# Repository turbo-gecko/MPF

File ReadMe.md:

# MPF

The MicroProfessor MPF-1 is one of the original Z80 trainers. It was a trainer that I suspect a lot of original Z80 coders first learned how to program the Z80, and it was my first introduction to programming the Z80. There is a multitude of information about the MPF-1 on the 'net so won't repeat it here.

With a more recent desire to go back and re-learn the Z80, I have managed to get hold of a couple of MPF-1's to re-live the experience. In hindsight. I can see just how limited the MPF-1 actually is. Part of it's issues for me are:
- Getting software on and off of the MPF-1 is via the keyboard or cassette tape.
- An incredibly tiny amount of RAM. Ideal for teaching the basics but not much else.
- Not a lot of options exist for expanding the capabilities of the MPF-1.

This repo is for the hardware and software I have developed for the MPF-1 (and other clones) that help overcome these drawbacks.

## How to expand the MPF-1
The following section descibes how to expand the capabilities of the MPF-1 to make use modern conveniences like serial download, SD card storage etc.

A non-negotiable goal though, is to provide expandability without modification to the original kit. The MPF-1 is after all, a piece of vintage computer equipment, and to physically modify it would take away from it's value as a piece of history. The following expansions make use of the Z80 CPU bus that is the top left 2x20 pin header connector.

The expansion bus of choice that works very well with the MPF-1 is the retro modern RCBus by Small Computer Central, and the RC2014 bus. An adapter card is required to connect the MPF-1 to the expansion bus and the designs are included in the Z80 Bus to RCBus folder.

### Basic expansion bus
A basic expansion bus will require as a minimum:
- RCBus backplane. The one in the photo is an SC112 https://smallcomputercentral.com/sc112-modular-backplane-rc2014/
- A power supply for the backplane. The one in the photo is an SC142 that has been modified to switch the incoming 9VDC to the MPF-1. This allows a single switch to power on/off the complete system. https://smallcomputercentral.com/sc142-power-module-rc2014/
- 40 pin ribbon cable to connect the MPF-1 to the backplane via the adapter.

This provides the necessary backplane, power and connectivity to expand the MPF-1.

### Adding additional memory
The MPF-1 comes with 2K of RAM fitted from 1800H to 1FFFH. This is insufficient for use with an expansion bus so the first card that should be obtained is a memory expansion card with a minimum of 32K such as:
- The 64K RAM module at https://z80kits.com/shop/64k-ram-module/ is a good choice. This is the module that is fitted in the backplane in the photo's. It has been configured to provide RAM from 4000H through to FFFFH, an additional 48K!
- Another module that I have experimented with is the Paged RAM module at https://smallcomputercentral.com/sc150-paged-ram-module-rc2014/. This can provide 32K from 8000H to FFFFH.

### High speed serial
The main way to enter programs into the MPF-1 is via the keypad as machine code. Whilst it is how the MPF-1 was envisaged to be used, it is a painfully slow and error-prone way of transferring programs to the MPF-1.

The expansion bus allows a serial card to be added and along with a hex download program, can make downloading hex files to the MPF-1 very easy and straightforward. The serial card in the photo's is an ACIA single serial card. https://smallcomputercentral.com/sc139-serial-68b50-module-rc2014/

### SD card storage
The only way to load and save programs with the MPF-1 is via audio files, traditionally on tape. Whilst there are modern ways around this, it is very slow, and you would need a program to convert compiled programs to an audio format.

To store and load files using an SD card only requires an I/O card and an Adafruit style SD card adapter. The I/O card in the photo is an SC129 https://smallcomputercentral.com/sc129-digital-i-o-rc2014/.

### Putting it all together
In the Software/Option ROM/ folder https://github.com/turbo-gecko/MPF/tree/main/Software/Option%20ROM is a binary file of an EPROM image that has the following software ready to run:
- 2000H - Hex download program.
- 2222H - Memory finder program.
- 2400H - Mini SD card reader program for loading files from slots 0-9 on the first SD carc virtual disk.

Burn the binary image to a 2732 EPROM and place it in the U7 socket on the MPF-1.

### Configuration

#### Serial
The software has been designed to work with an ACIA serial card only (more in the works) at I/O address C8H. The hex load and SD card programs are designed to use the serial card at 115kbps with RTS/CTS handshaking. There is further information on the serial card at https://github.com/turbo-gecko/MPF/tree/main/Software/Hex%20Load

#### SD Card
The I/O card should be configured to use address FDH, however this can be modified along with the pin configurations in the spi_IO.ASM file at https://github.com/turbo-gecko/MPF/tree/main/Software/Library.

Default pin configurations as follows:
| I/O | Pin | Description |
| --- | --- | ----------- |
| In  |  7  | MISO        |
| Out |  0  | MOSI        |
| Out |  1  | CLK         |
| Out |  2  | CS          |

Make sure that the SD card module is designed to run off 5VDC and has the 3V3 reg on board to drive the SD card correctly.

### Using the expansion cards
Once you have everything up and running, including the U7 ROM, you can try using the hex load program at 2000H to download the 'HELPUS' example (helpus.hex) from https://github.com/turbo-gecko/MPF/tree/main/Software/Work%20Book%20Examples. Download the hex file and run the program at 1800H.

### Troubleshooting
- Start with the backplane, power supply and ribbon cable first. Make sure that when both the backplane and the MPF-1 is powered on, the MPF-1 works as normal.
- Power off the system, add the expansion cards one at a time, power back on and confirm the MPF-1 is working. If it isn't check
  - The ribbon cable is connected correctly. Pin 1 on the MPF-1 is at the top, Pin 1 on the adapter card is towards the 45 degree angle on the PCB. (See photo for details)
  - The expansion card is seated correctly in the backplane.

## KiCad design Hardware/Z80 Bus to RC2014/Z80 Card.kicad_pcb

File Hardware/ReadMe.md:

# Hardware Stuff

## Bezel - 3D Printer files
Bezel for the 7 segment display to hold the red filter lens in place.

## Z80 Bus to RCBus
Adapter card to enable the use of an RCBus or RC2014 style backplane to extend the Z80 bus of the MPF-1.

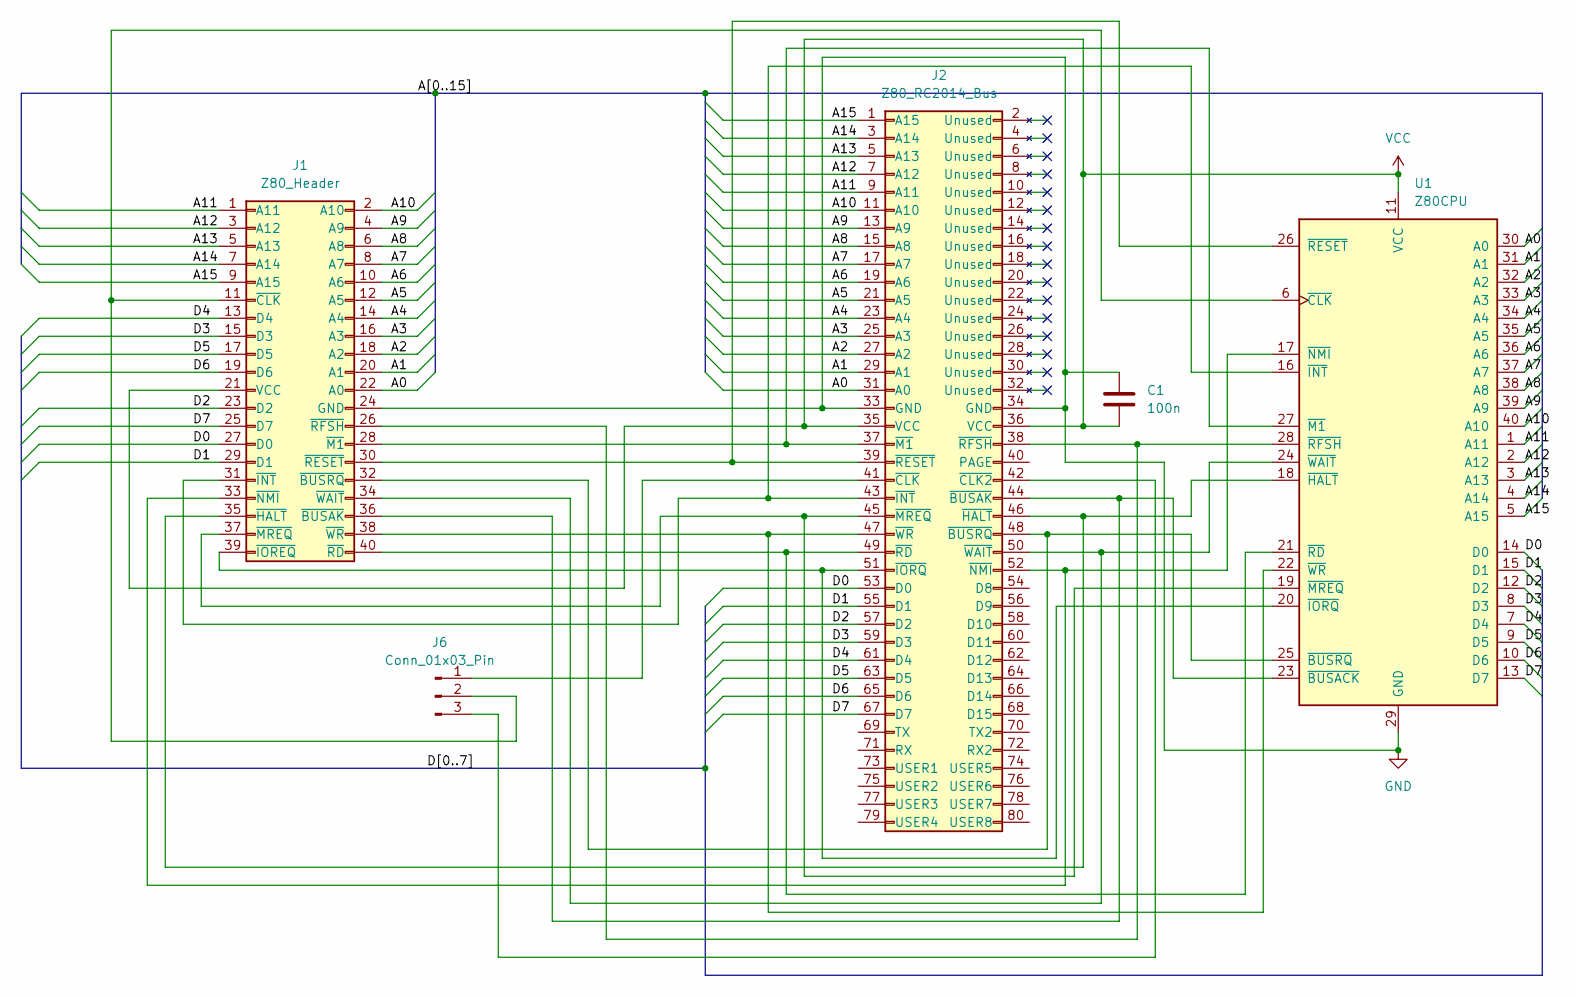
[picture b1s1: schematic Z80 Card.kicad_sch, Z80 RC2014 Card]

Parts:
C1: 100n; C_Rect_L4.0mm_W2.5mm_P2.50mm
J1: Z80_Header; PinSocket_2x20_P2.54mm_Vertical
J2: Z80_RC2014_Bus; PinSocket_2x40_P2.54mm_Vertical
J6: Conn_01x03_Pin; PinHeader_1x03_P2.54mm_Vertical
U1: Z80CPU; DIP-40_W15.24mm_Socket

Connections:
/A0: J1.22 (A0), J2.31 (A0), U1.30 (A0)
/A1: J1.20 (A1), J2.29 (A1), U1.31 (A1)
/A2: J1.18 (A2), J2.27 (A2), U1.32 (A2)
/A3: J1.16 (A3), J2.25 (A3), U1.33 (A3)
/A4: J1.14 (A4), J2.23 (A4), U1.34 (A4)
/A5: J1.12 (A5), J2.21 (A5), U1.35 (A5)
/A6: J1.10 (A6), J2.19 (A6), U1.36 (A6)
/A7: J1.8 (A7), J2.17 (A7), U1.37 (A7)
/A8: J1.6 (A8), J2.15 (A8), U1.38 (A8)
/A9: J1.4 (A9), J2.13 (A9), U1.39 (A9)
/A10: J1.2 (A10), J2.11 (A10), U1.40 (A10)
/A11: J1.1 (A11), J2.9 (A11), U1.1 (A11)
/A12: J1.3 (A12), J2.7 (A12), U1.2 (A12)
/A13: J1.5 (A13), J2.5 (A13), U1.3 (A13)
/A14: J1.7 (A14), J2.3 (A14), U1.4 (A14)
/A15: J1.9 (A15), J2.1 (A15), U1.5 (A15)
/D0: J1.27 (D0), J2.53 (D0), U1.14 (D0)
/D1: J1.29 (D1), J2.55 (D1), U1.15 (D1)
/D2: J1.23 (D2), J2.57 (D2), U1.12 (D2)
/D3: J1.15 (D3), J2.59 (D3), U1.8 (D3)
/D4: J1.13 (D4), J2.61 (D4), U1.7 (D4)
/D5: J1.17 (D5), J2.63 (D5), U1.9 (D5)
/D6: J1.19 (D6), J2.65 (D6), U1.10 (D6)
/D7: J1.25 (D7), J2.67 (D7), U1.13 (D7)
GND: C1.1, J1.24 (GND), J2.33 (GND), J2.34 (GND), U1.29 (GND)
unnamed: J1.36 (~BUSAK), J2.44 (~BUSAK), U1.23 (~BUSACK)
unnamed: J1.32 (~BUSRQ), J2.48 (~BUSRQ), U1.25 (~BUSRQ)
unnamed: J1.11 (~CLK), J6.2, U1.6 (~CLK)
unnamed: J1.35 (~HALT), J2.46 (~HALT), U1.18 (~HALT)
unnamed: J1.31 (~INT), J2.43 (~INT), U1.16 (~INT)
unnamed: J1.39 (~IOREQ), J2.51 (~IORQ), U1.20 (~IORQ)
unnamed: J1.28 (~M1), J2.37 (~M1), U1.27 (~M1)
unnamed: J1.37 (~MREQ), J2.45 (~MREQ), U1.19 (~MREQ)
unnamed: J1.33 (~NMI), J2.52 (~NMI), U1.17 (~NMI)
unnamed: J1.40 (~RD), J2.49 (~RD), U1.21 (~RD)
unnamed: J1.30 (~RESET), J2.39 (~RESET), U1.26 (~RESET)
unnamed: J1.26 (~RFSH), J2.38 (~RFSH), U1.28 (~RFSH)
unnamed: J1.34 (~WAIT), J2.50 (~WAIT), U1.24 (~WAIT)
unnamed: J1.38 (~WR), J2.47 (~WR), U1.22 (~WR)
unnamed: J2.42 (~CLK2), J6.3
unnamed: J2.41 (~CLK), J6.1
VCC: C1.2, J1.21 (VCC), J2.35 (VCC), J2.36 (VCC), U1.11 (VCC)

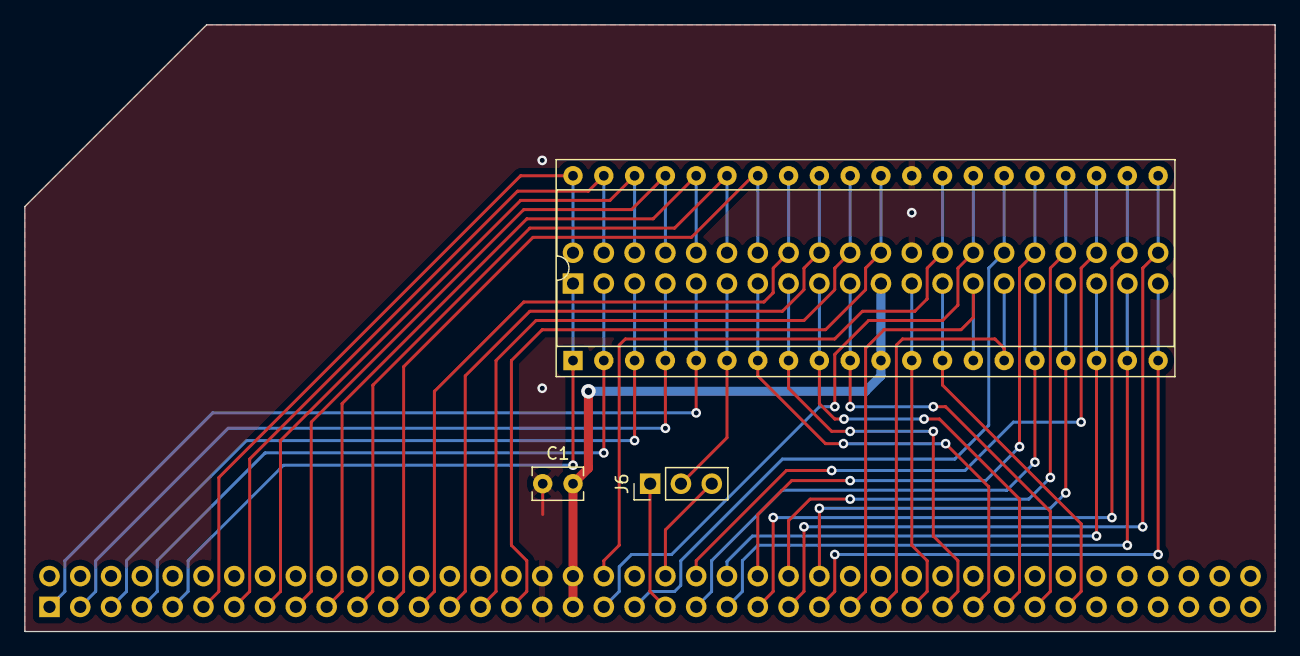
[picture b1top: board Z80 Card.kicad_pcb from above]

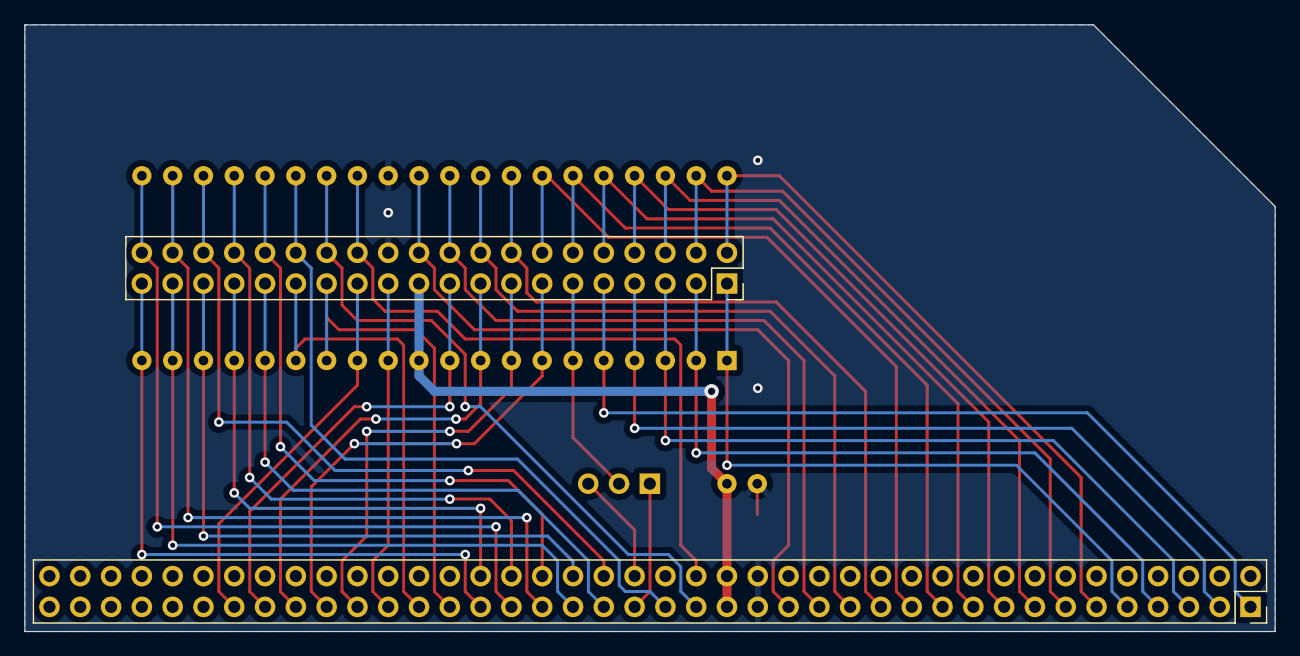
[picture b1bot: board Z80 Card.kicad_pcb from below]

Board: 2 copper layers, 103.1 x 50.0 mm, 5 parts (2 on the bottom side), 42 nets.

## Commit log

2024-04-10 v1.1 - RTS flow control added
2024-04-11 Moved example files to own folder
2024-04-11 Added serial photos
2024-04-12 v1.2 - Re-enabled RTS flow control on exit
2024-04-27 Added more workbook examples
2024-04-27 Added mpf-1.asm
2024-04-27 Updated style
2024-04-27 Added original MPF-1 ROM image
2024-04-27 Added listing file generated from mpf-1.asm
2024-04-27 Added 3D printer files for 7-Segment display surround
2024-07-27 MinSD v1.0
    Initial commit.
2024-07-27 Moved MinSD to own folder
2024-07-27 Renamed md file
2024-07-27 MinOS v0.2
2024-07-28 MinOS v0.3
2024-07-31 v0.4
2024-07-31 v1.1 update
    Moved RAM .org closer to top of RAM.
    Merged SPI code.
2024-08-04 MinOS v1.0.0
2024-08-04 Added Memtest
2024-08-04 Updated ROM locations
2024-08-04 Folder re-org
2024-08-04 Updated ReadMe Files
2024-08-04 Initial upload
2024-08-04 Updated Z80 Bus to RCBus
2024-08-04 Rebuild for 1800H
2024-08-11 MinOS v1.1.0
2024-08-11 v1.1.1
    Refer to the Release Notes.md file for details.
2024-08-13 v1.3 update
2024-08-13 v1.4 updates
2024-08-13 v1.1 updates
2024-08-13 v1.2 updates
2024-08-14 v1.4 update
2024-08-17 Added archive folder to the ignore list
2024-08-18 Updated libraries
2024-08-18 MinOS v1.5 updates
2024-08-24 Updated example programs
2024-08-24 Added user manual examples
2024-08-26 Updated examples
2024-08-27 Updated ROM v1.0
2024-09-14 Added photos
2024-09-14 Revert "Added photos"
    This reverts commit 3fc4c098c01cdf143c627283cc083e645772e4c6.
2024-09-14 Reapply "Added photos"
    This reverts commit e72a031ba3540b7ec12a02bfea7f2fc7457aef3b.
2024-09-14 Revert "Reapply "Added photos""
    This reverts commit 914f262f197c9a461f3b4bc8786a6cf1493aca2c.
2024-09-14 Added photo's
2024-09-14 Moved photo's
2024-09-14 Added library files
2024-09-14 Updated MinSD files
2024-09-14 Fixes for ROM calls
2024-09-15 v1.2 update
    Fixed issue with being unable to save 8200H bytes or more
2024-09-15 v1.6.1 Debug build
    Fixed issues with error messages
    Added code and data start/end addresses to 'ver' command
    Added simple checksum to 'ver' command
2024-09-15 Recompiled with updated sd_base.asm
    Recompiled with updated
